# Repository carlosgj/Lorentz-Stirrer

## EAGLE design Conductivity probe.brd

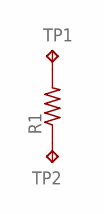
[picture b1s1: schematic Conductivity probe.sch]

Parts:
R1: R-US_0204/7; 0204/7
TP1, TP2: TPPAD1-17; P1-17

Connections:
unnamed: R1.2, TP1.TP
unnamed: R1.1, TP2.TP

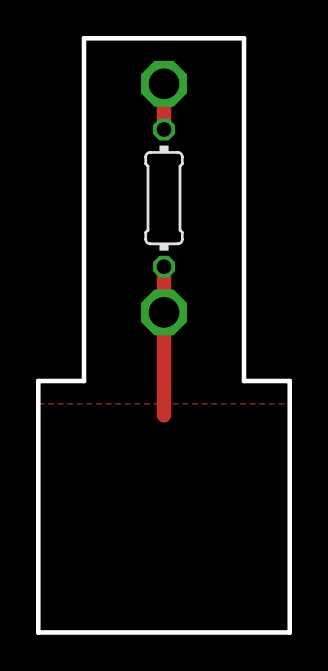
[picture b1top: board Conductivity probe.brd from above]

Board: 2 copper layers, 14.0 x 33.0 mm, 3 parts (0 on the bottom side), 2 nets.

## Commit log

2016-08-16 Initial
2016-08-16 Quadrupole
2016-08-16 Iron cap
2016-08-16 Iron ring
2016-08-16 Version updates, apparently
2016-08-16 Ignore
2016-09-11 CAD Updates
2016-09-11 no message
2016-10-17 Reorg
2016-10-17 Upconvert & change to quadrature
2016-10-18 Updated CAD
2016-10-20 Changed to load cell
2016-10-25 Generated image
2016-10-25 Added AVI
2016-10-25 ignores
2016-10-25 Updated pictures
2016-10-26 Control system components
2016-10-26 Control system
2016-10-27 Simplified shape
2016-10-31 Added gif
2016-11-07 Updates for machinability
2016-11-07 Shallow container
2016-11-11 Instability analysis
2016-11-12 Conductivity experiment
2016-11-12 Old stuff
2016-11-12 More old stuff
2016-11-17 Added gearbox, changed to steel shaft
2016-11-21 Misc
2016-12-03 Writeup work
2016-12-03 Analysis
2016-12-12 Writeup updates
2016-12-13 Presentation
2016-12-14 Presentation PDF
2016-12-17 Work on report
2017-01-05 Investigation of axial solenoid
2017-02-09 Added gearbox & rearranged electronics panel
2017-02-23 Updates to gearbox
2017-03-15 Added aero cowling
2017-06-16 Misc updates
